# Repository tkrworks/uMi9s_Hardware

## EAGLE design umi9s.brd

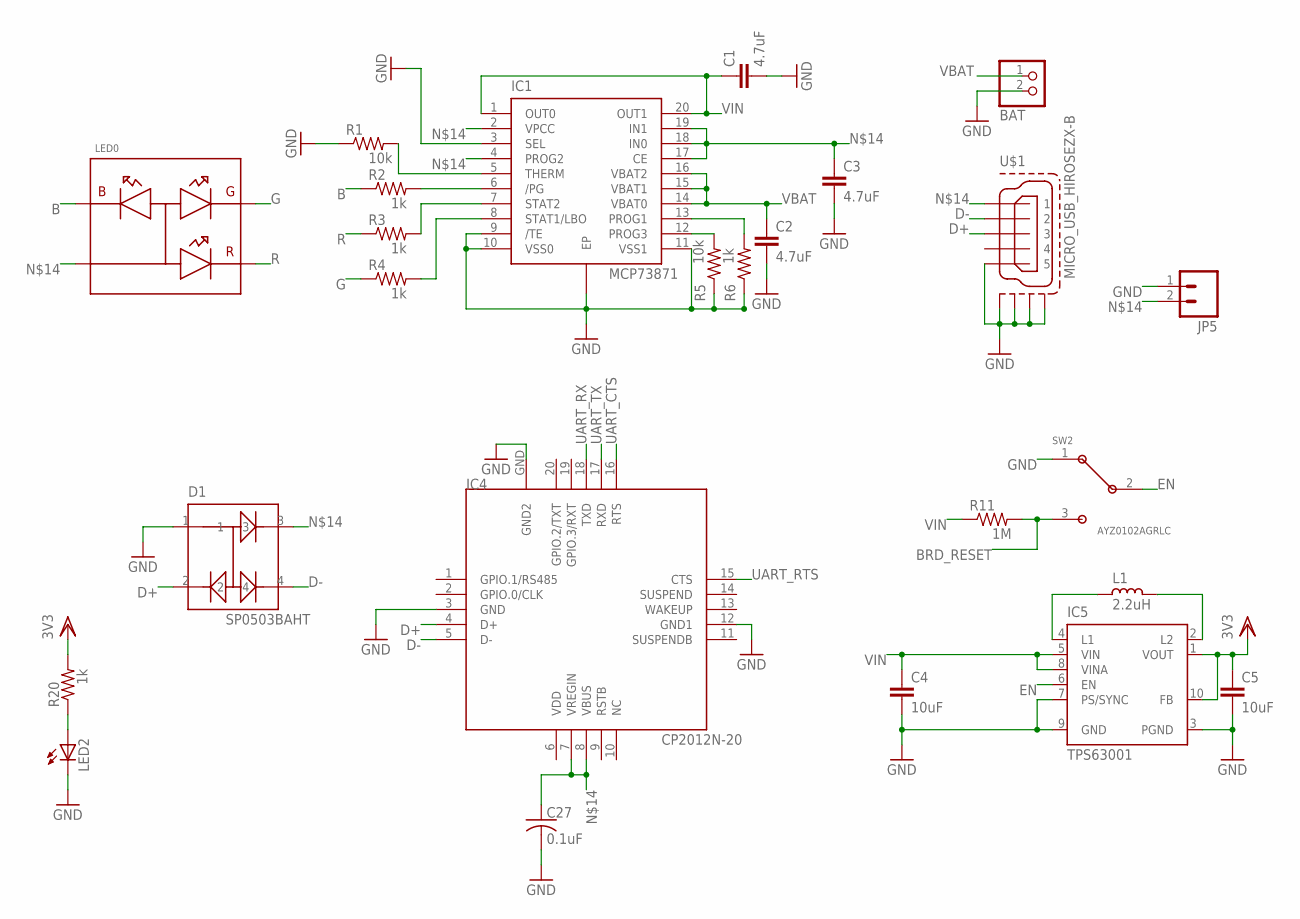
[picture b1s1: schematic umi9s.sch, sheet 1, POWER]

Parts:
BAT: JST_2PIN-SMT; JST-PH-2-SMT
C1, C2, C3: 4.7uF; C2012
C4, C5: 10uF; C2012
C27: 0.1uF; C0402
D1: SP0503BAHT; SOT143
IC1: MCP73871; QFN20
IC4: CP2012N-20; CP2102-QFN20
IC5: TPS63001; DRC-S-PVSON-N10
JP5: M02PTH; 1X02
L1: 2.2uH; L1210
LED0: APFA2507LQBDSEEZGKC; 2507_RA_SMD_LED
LED2: LEDCHIPLED_0603; CHIPLED_0603
R1, R5: 10k; 0402-RES
R2, R3, R4, R6, R20: 1k; 0402-RES
R11: 1M; 0402-RES
SW2: AYZ0102AGRLC
U$1: MICRO_USB_HIROSEZX-B; MICRO_USB_HIROSE_B

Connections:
B: LED0.1 (B), R2.1
BRD_RESET: R11.2, SW2.3; also elsewhere on the board
D+: D1.2, IC4.4 (D+), U$1.P$3 (3)
D-: D1.4, IC4.5 (D-), U$1.P$2 (2)
EN: IC5.6 (EN), SW2.2
G: LED0.4 (G), R4.1
GND: BAT.2 (1), C1.2, C2.2, C3.2, C4.2, C5.2, C27.2, D1.1, IC1.3 (SEL), IC1.9 (/TE), IC1.10 (VSS0), IC1.11 (VSS1), IC1.EP, IC4.3 (GND), IC4.12 (GND1), IC4.GND (GND2), IC5.3 (PGND), IC5.7 (PS/SYNC), IC5.9 (GND), JP5.1, LED2.C, R1.1, R5.1, R6.1, SW2.1, U$1.P$5 (5), U$1.S1, U$1.S2, U$1.S3, U$1.S4; also elsewhere on the board
unnamed: IC5.4 (L1), L1.2
unnamed: IC5.2 (L2), L1.1
unnamed: C3.1, C27.1, D1.3, IC1.2 (VPCC), IC1.4 (PROG2), IC1.17 (CE), IC1.18 (IN0), IC1.19 (IN1), IC4.7 (VREGIN), IC4.8 (VBUS), JP5.2, LED0.2 (A), U$1.P$1 (1)
unnamed: IC1.6 (/PG), R2.2
unnamed: IC1.7 (STAT2), R3.2
unnamed: LED2.A, R20.1
unnamed: IC1.8 (STAT1/LBO), R4.2
unnamed: IC1.5 (THERM), R1.2
unnamed: IC1.12 (PROG3), R5.2
unnamed: IC1.13 (PROG1), R6.2
R: LED0.3 (R), R3.1
UART_CTS: IC4.16 (RTS); also elsewhere on the board
UART_RTS: IC4.15 (CTS); also elsewhere on the board
UART_RX: IC4.18 (TXD); also elsewhere on the board
UART_TX: IC4.17 (RXD); also elsewhere on the board
VBAT: BAT.1 (2), C2.1, IC1.14 (VBAT0), IC1.15 (VBAT1), IC1.16 (VBAT2)
VDD: C5.1, IC4.6 (VDD), IC5.1 (VOUT), IC5.10 (FB), R20.2; also elsewhere on the board
VIN: C1.1, C4.1, IC1.1 (OUT0), IC1.20 (OUT1), IC5.5 (VIN), IC5.8 (VINA), R11.1

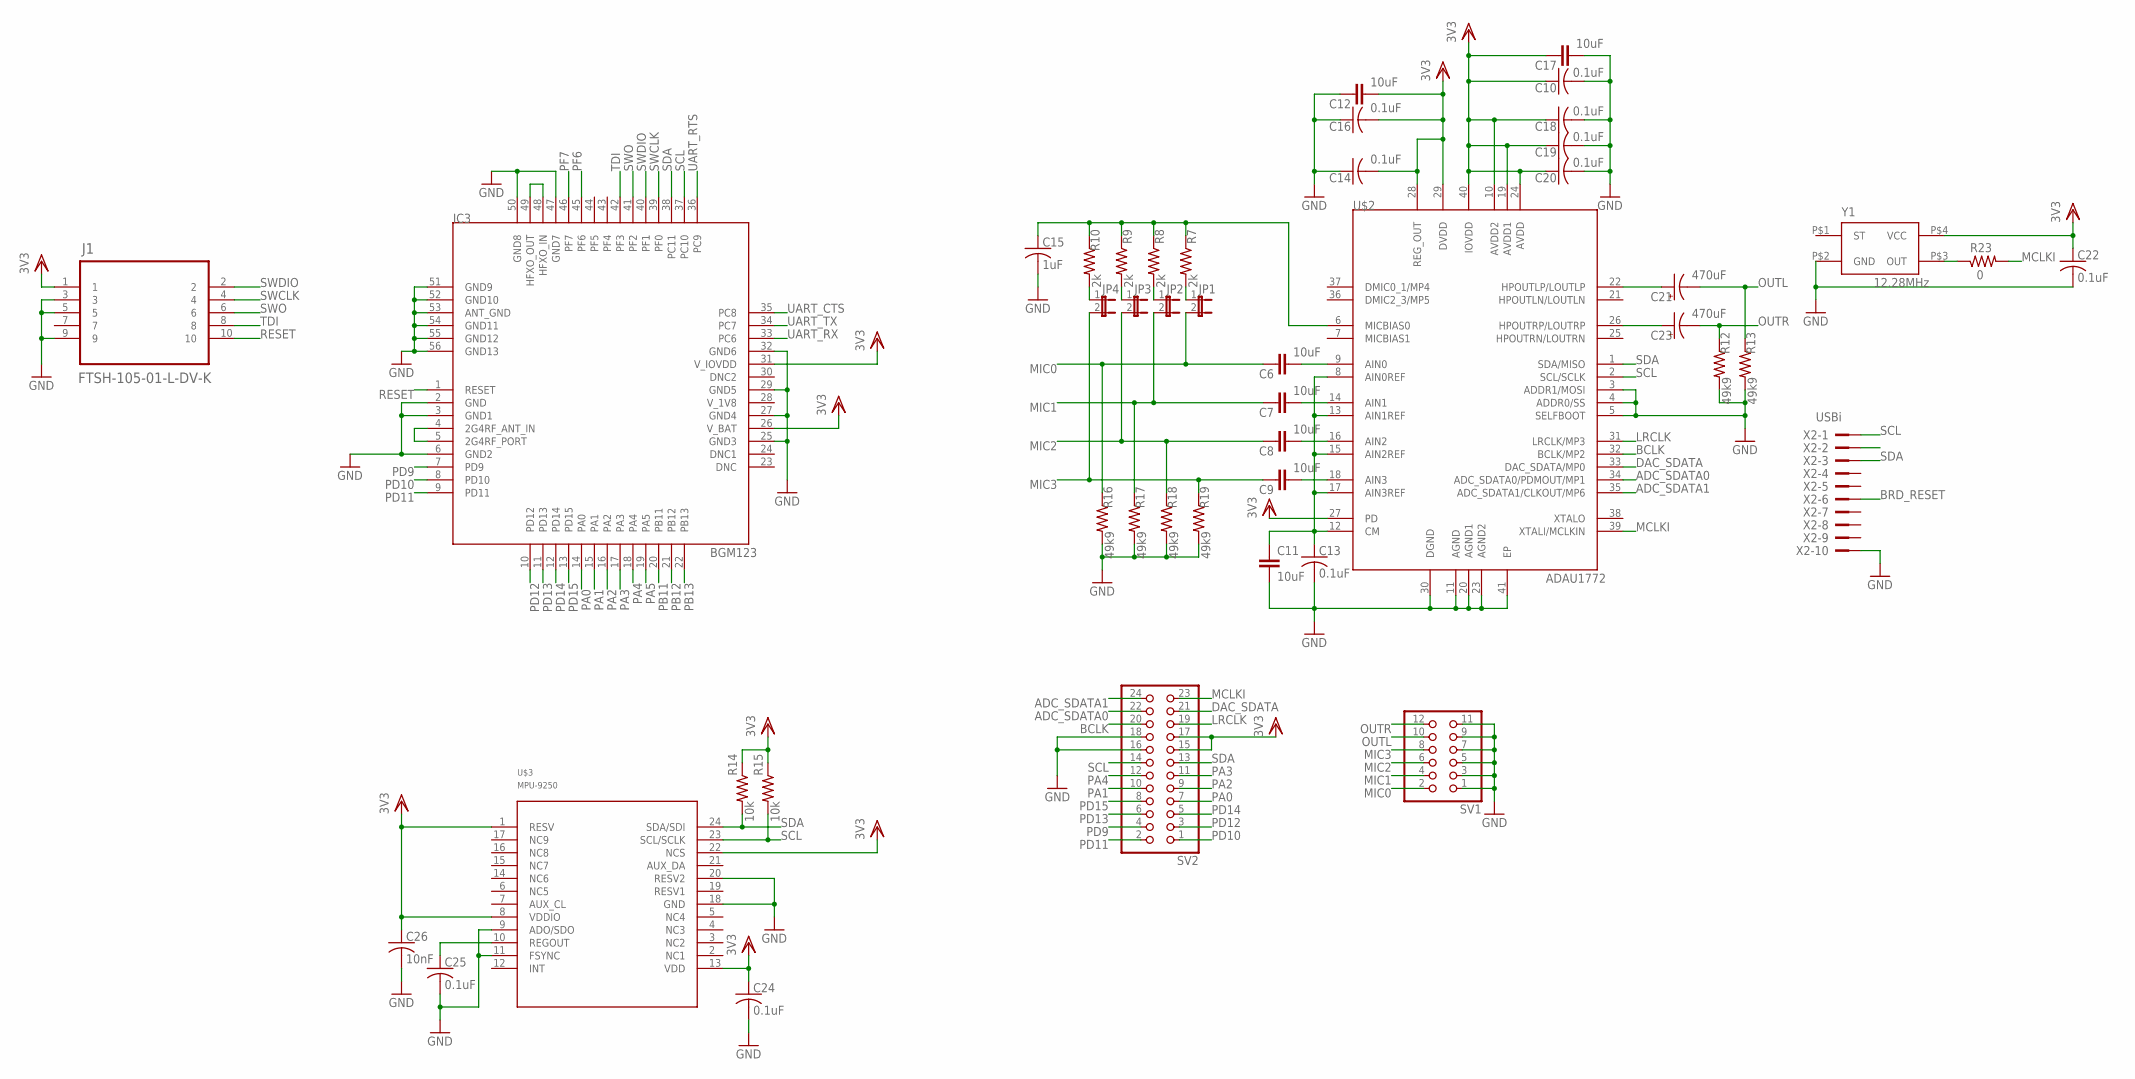
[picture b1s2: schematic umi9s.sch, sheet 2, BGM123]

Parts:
C6, C7, C8, C9, C11, C12, C17: 10uF; C2012
C10, C13, C14, C16, C18, C19, C20, C22, C24, C25: 0.1uF; C0402
C15: 1uF; C0402
C21, C23: 470uF; B/3528-21R
C26: 10nF; C0402
IC3: BGM123; BGM12X
J1: FTSH-105-01-L-DV-K; SAMTEC_FTSH-105-01-L-DV-K
JP1, JP2, JP3, JP4: JUMPER-2SMD-NO; SJ_2S-NO
R7, R8, R9, R10: 2k; 0402-RES
R12, R13, R16, R17, R18, R19: 49k9; 0402-RES
R14, R15: 10k; 0402-RES
R23: 0; 0402-RES
SV1: PINHD-2X06; 2X06ROUND
SV2: PINHD-2X12; 2X12ROUND
U$2: ADAU1772; QFN40_600X600
U$3: MPU-9250; LEAD-QFN24
X2: USBi; PAK100/2500-10
Y1: 12.28MHz; SG-210

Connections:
ADC_SDATA0: SV2.22, U$2.34 (ADC_SDATA0/PDMOUT/MP1)
ADC_SDATA1: SV2.24, U$2.35 (ADC_SDATA1/CLKOUT/MP6)
AIN0: C6.2, U$2.9 (AIN0)
AIN1: C7.2, U$2.14 (AIN1)
AIN2: C8.2, U$2.16 (AIN2)
AIN3: C9.2, U$2.18 (AIN3)
BCLK: SV2.20, U$2.32 (BCLK/MP2)
BRD_RESET: X2.6; also elsewhere on the board
CM: C11.1, C13.1, U$2.8 (AIN0REF), U$2.12 (CM), U$2.13 (AIN1REF), U$2.15 (AIN2REF), U$2.17 (AIN3REF)
DAC_SDATA: SV2.21, U$2.33 (DAC_SDATA/MP0)
DNC2: IC3.30 (DNC2)
GND: C10.2, C11.2, C12.1, C13.2, C14.1, C15.2, C16.1, C17.2, C18.2, C19.2, C20.2, C22.2, C24.2, C25.2, C26.2, IC3.2 (GND), IC3.3 (GND1), IC3.6 (GND2), IC3.25 (GND3), IC3.27 (GND4), IC3.29 (GND5), IC3.32 (GND6), IC3.47 (GND7), IC3.50 (GND8), IC3.51 (GND9), IC3.52 (GND10), IC3.53 (ANT_GND), IC3.54 (GND11), IC3.55 (GND12), IC3.56 (GND13), J1.3, J1.5, J1.9, R12.2, R13.2, R16.2, R17.2, R18.2, R19.2, SV1.1, SV1.3, SV1.5, SV1.7, SV1.9, SV1.11, SV2.16, SV2.18, U$2.3 (ADDR1/MOSI), U$2.4 (ADDR0/SS), U$2.5 (SELFBOOT), U$2.11 (AGND), U$2.20 (AGND1), U$2.23 (AGND2), U$2.30 (DGND), U$2.41 (EP), U$3.9 (ADO/SDO), U$3.11 (FSYNC), U$3.18 (GND), U$3.20 (RESV2), X2.10, Y1.P$2 (GND); also elsewhere on the board
HPOUTL: C21.+, U$2.22 (HPOUTLP/LOUTLP)
HPOUTR: C23.+, U$2.26 (HPOUTRP/LOUTRP)
LRCLK: SV2.19, U$2.31 (LRCLK/MP3)
MCLKI: R23.2, SV2.23, U$2.39 (XTALI/MCLKIN)
MIC0: C6.1, JP1.2, R16.1, SV1.2
MIC1: C7.1, JP2.2, R17.1, SV1.4
MIC2: C8.1, JP3.2, R18.1, SV1.6
MIC3: C9.1, JP4.2, R19.1, SV1.8
MICBIAS0: C15.1, R7.1, R8.1, R9.1, R10.1, U$2.6 (MICBIAS0)
unnamed: IC3.48 (HFXO_IN), IC3.49 (HFXO_OUT)
unnamed: IC3.4 (2G4RF_ANT_IN), IC3.5 (2G4RF_PORT)
unnamed: C25.1, U$3.10 (REGOUT)
unnamed: JP1.1, R7.2
unnamed: JP2.1, R8.2
unnamed: JP3.1, R9.2
unnamed: R23.1, Y1.P$3 (OUT)
unnamed: JP4.1, R10.2
OUTL: C21.-, R13.1, SV1.10
OUTR: C23.-, R12.1, SV1.12
PA0: IC3.14 (PA0), SV2.7
PA1: IC3.15 (PA1), SV2.10
PA2: IC3.16 (PA2), SV2.9
PA3: IC3.17 (PA3), SV2.11
PA4: IC3.18 (PA4), SV2.12
PA5: IC3.19 (PA5)
PB11: IC3.20 (PB11)
PB12: IC3.21 (PB12)
PB13: IC3.22 (PB13)
PD9: IC3.7 (PD9), SV2.4
PD10: IC3.8 (PD10), SV2.1
PD11: IC3.9 (PD11), SV2.2
PD12: IC3.10 (PD12), SV2.3
PD13: IC3.11 (PD13), SV2.6
PD14: IC3.12 (PD14), SV2.5
PD15: IC3.13 (PD15), SV2.8
PF6: IC3.45 (PF6)
PF7: IC3.46 (PF7)
RESET: IC3.1 (RESET), J1.10
SCL: IC3.37 (PC10), R15.2, SV2.14, U$2.2 (SCL/SCLK), U$3.23 (SCL/SCLK), X2.1
SDA: IC3.38 (PC11), R14.2, SV2.13, U$2.1 (SDA/MISO), U$3.24 (SDA/SDI), X2.3
SWCLK: IC3.39 (PF0), J1.4
SWDIO: IC3.40 (PF1), J1.2
SWO: IC3.41 (PF2), J1.6
TDI: IC3.42 (PF3), J1.8
UART_CTS: IC3.35 (PC8); also elsewhere on the board
UART_RTS: IC3.36 (PC9); also elsewhere on the board
UART_RX: IC3.33 (PC6); also elsewhere on the board
UART_TX: IC3.34 (PC7); also elsewhere on the board
VDD: C10.1, C12.2, C14.2, C16.2, C17.1, C18.1, C19.1, C20.1, C22.1, C24.1, C26.1, IC3.26 (V_BAT), IC3.31 (V_IOVDD), J1.1, R14.1, R15.1, SV2.15, SV2.17, U$2.10 (AVDD2), U$2.19 (AVDD1), U$2.24 (AVDD), U$2.27 (PD), U$2.28 (REG_OUT), U$2.29 (DVDD), U$2.40 (IOVDD), U$3.1 (RESV), U$3.8 (VDDIO), U$3.13 (VDD), U$3.22 (NCS), Y1.P$4 (VCC); also elsewhere on the board
V_1V8: IC3.28 (V_1V8)

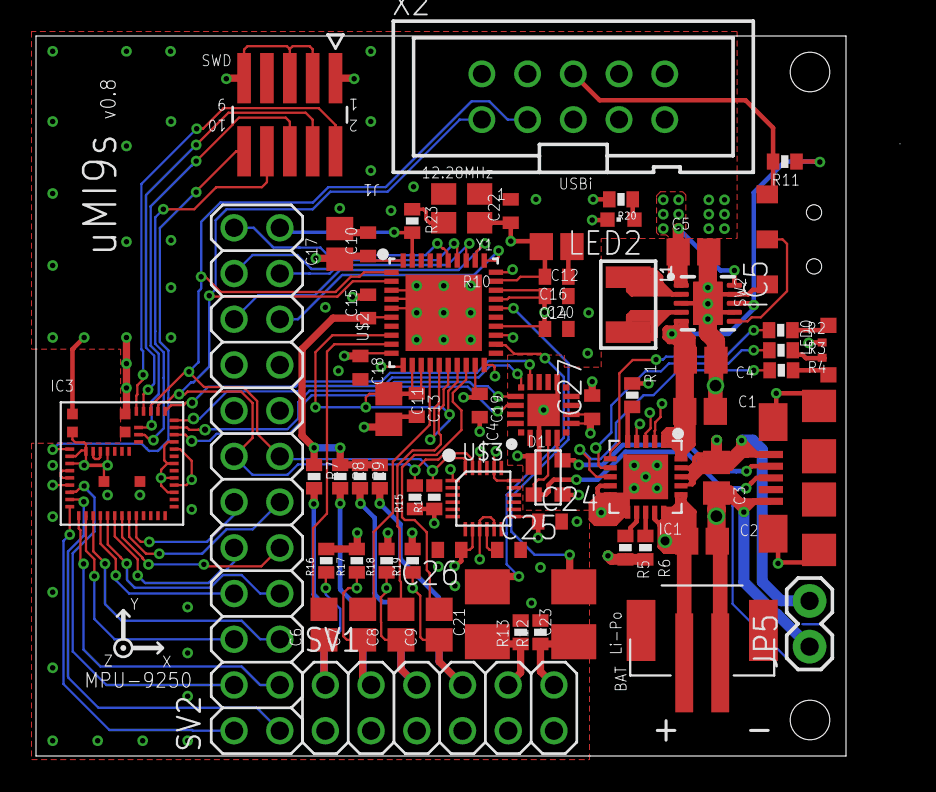
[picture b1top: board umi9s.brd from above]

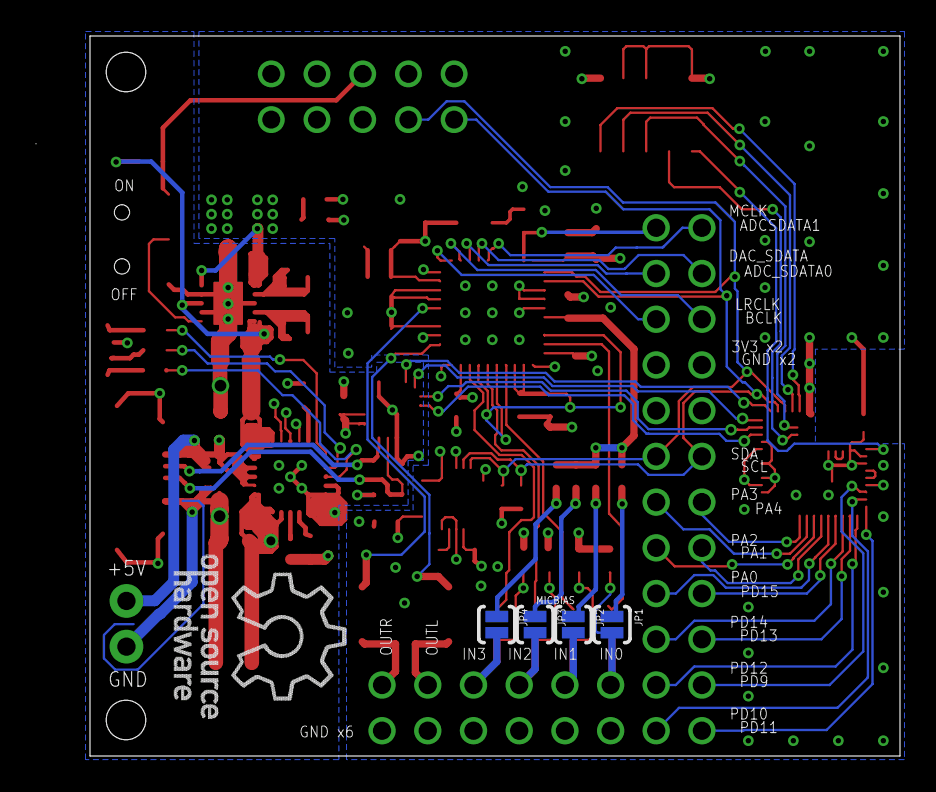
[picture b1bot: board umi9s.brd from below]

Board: 4 copper layers, 48.0 x 40.0 mm, 71 parts (4 on the bottom side), 72 nets.

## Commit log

2018-04-16 Add eagle.epf.
2018-04-16 Add .sch and .brd files.
2018-04-16 Release v0.5.
2018-04-16 Release v0.6.
2018-04-16 Release v0.7.
2018-04-16 Release v0.8.
    Rename from mcmc12 to uMi9s.
2018-04-16 Update .epf file.
2018-04-16 Add the gerber files.

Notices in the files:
parts and their libraries:
SparkFun: Licensing: CC v3.0 Share-Alike You are welcome to use this library for commercial purposes.
rc-master-smd: Copyright (C) 2007, Bob Starr
